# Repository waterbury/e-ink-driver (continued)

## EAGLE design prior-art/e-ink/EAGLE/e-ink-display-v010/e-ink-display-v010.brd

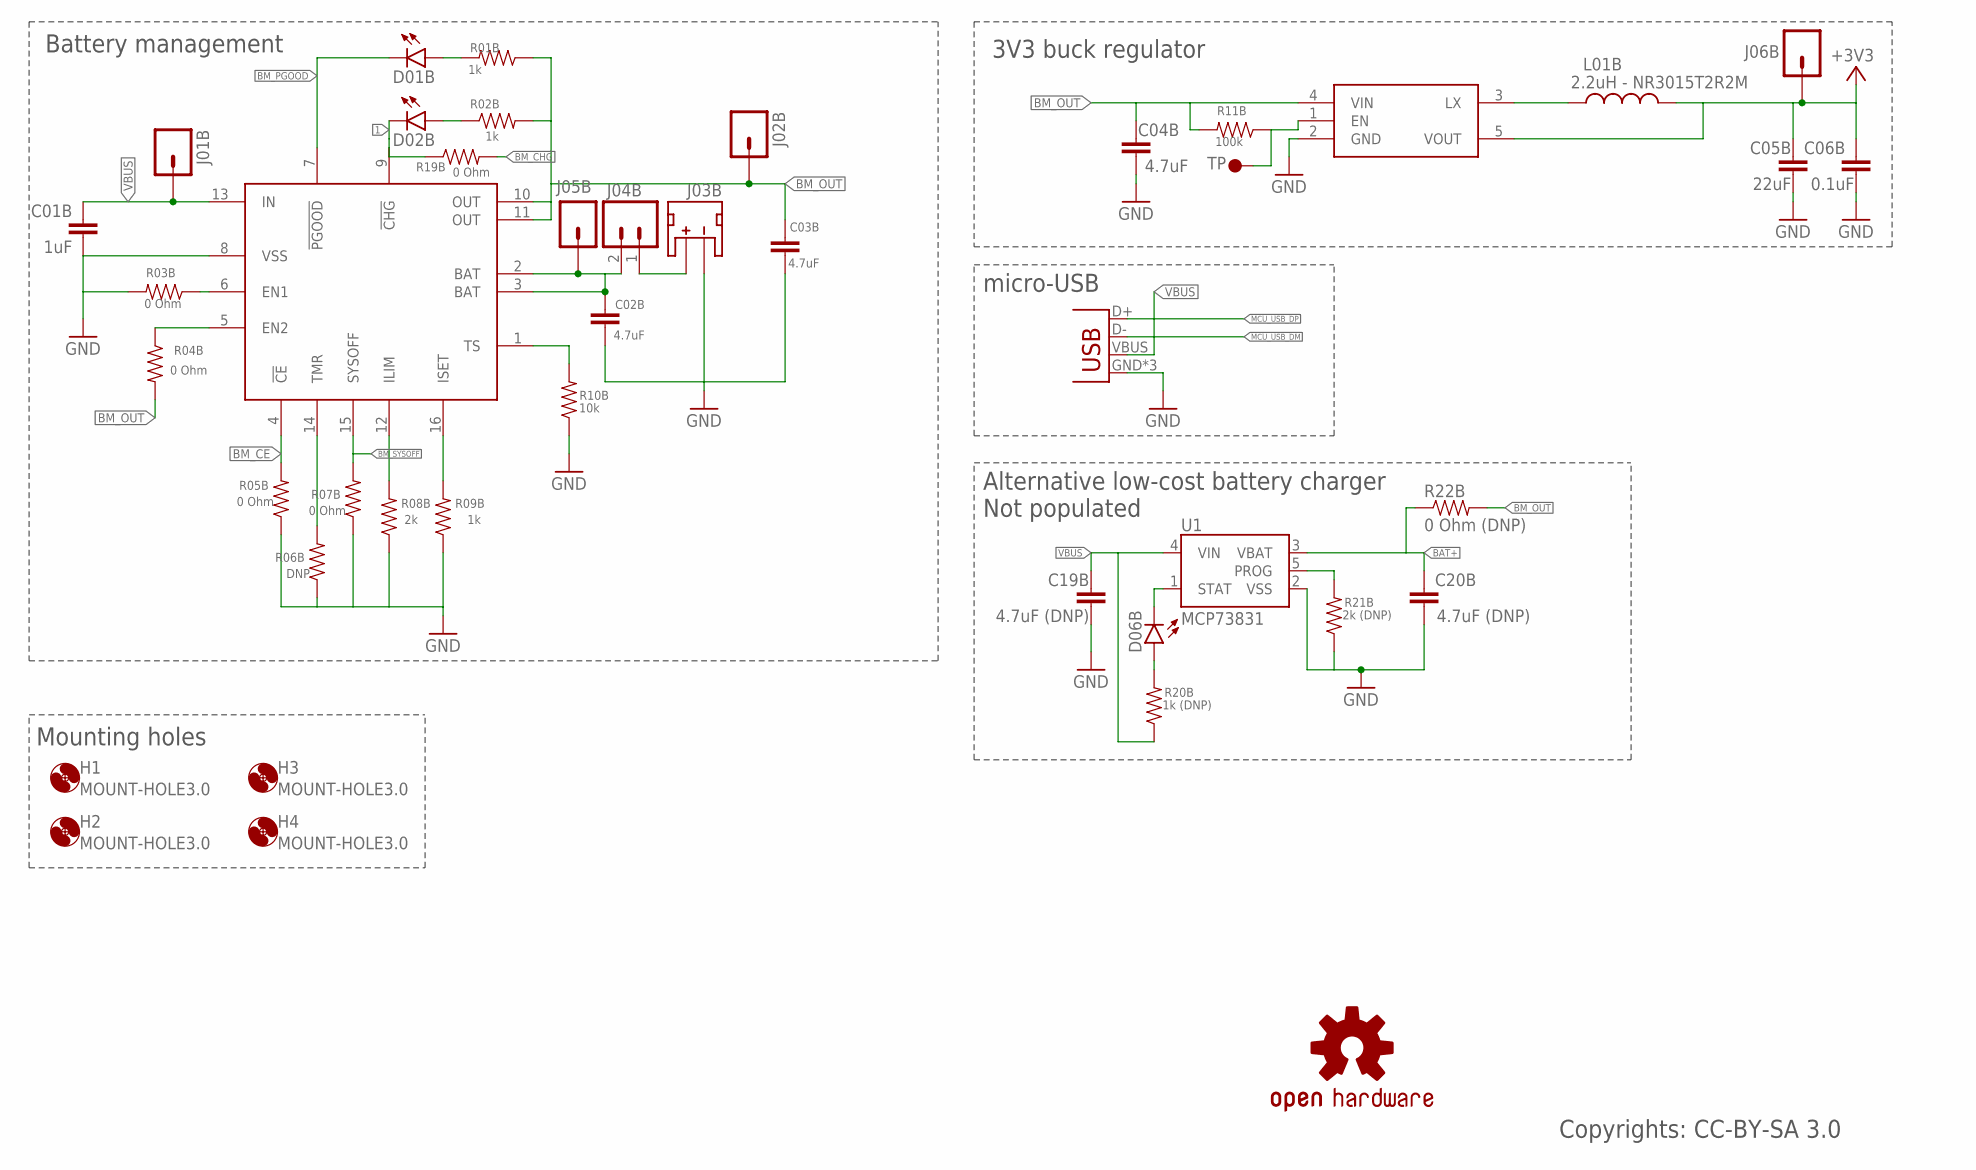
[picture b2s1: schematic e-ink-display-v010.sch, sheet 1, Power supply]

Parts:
C01B: 1uF; 0603-CAP
C02B, C03B, C04B: 4.7uF; 0603-CAP
C05B: 22uF; 0603-CAP
C06B: 0.1uF; 0603-CAP
C19B, C20B: 4.7uF (DNP); 0603-CAP
D01B, D02B, D06B: LED0603; LED-0603
H1, H2, H3, H4: MOUNT-HOLE3.0; 3,0
J01B, J02B, J05B, J06B: M01PTH; 1X01
J03B: JST_2MM_MALE; JST-2-SMD
J04B: M02PTH; 1X02
J07B: USBUSB-MICROB-SLOT-HOLE; USB-MICROB-SLOT-HOLE
L01B: 2.2uH - NR3015T2R2M; INDUCTOR-NR3015
LOGO1: OSHW-LOGOPAD; OSHW-LOGO-M-PAD
R01B, R02B, R09B: 1k; 0603-RES
R03B, R04B, R05B, R07B, R19B: 0 Ohm; 0603-RES
R06B: DNP; 0603-RES
R08B: 2k; 0603-RES
R10B: 10k; 0603-RES
R11B: 100k; 0603-RES
R20B: 1k (DNP); 0603-RES
R21B: 2k (DNP); 0603-RES
R22B: 0 Ohm (DNP); 1206
TP01B: TP1; TP35_BOT
U1: MCP73831; SOT23-5
U01B: BQ24075; PVQFN-16
U02B: R8008-33; SOT23-5

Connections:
1: D02B.C, R19B.1, U01B.9 (!CHG)
+3V3: C05B.2, C06B.2, J06B.1, L01B.2, U02B.5 (VOUT); also elsewhere on the board
BAT+: C20B.2, J03B.2 (+), J04B.1, R22B.1, U1.3 (VBAT)
BM_BAT: C02B.2, J04B.2, J05B.1, U01B.2 (BAT), U01B.3 (BAT)
BM_CE: R05B.2, U01B.4 (!CE)
BM_CHG: R19B.2; also elsewhere on the board
BM_OUT: C03B.2, C04B.2, J02B.1, R01B.1, R02B.2, R04B.2, R11B.2, R22B.2, U01B.10 (OUT), U01B.11 (OUT), U02B.4 (VIN); also elsewhere on the board
BM_PGOOD: D01B.C, U01B.7 (!PGOOD); also elsewhere on the board
BM_SYSOFF: R07B.2, U01B.15 (SYSOFF)
GND: C01B.1, C02B.1, C03B.1, C04B.1, C05B.1, C06B.1, C19B.1, C20B.1, J03B.1 (-), J07B.GND, J07B.MT1 (GND), J07B.MT2 (GND), R03B.2, R05B.1, R06B.1, R07B.1, R08B.1, R09B.1, R10B.1, R21B.1, U1.2 (VSS), U01B.8 (VSS), U02B.2 (GND); also elsewhere on the board
MCU_USB_DM: J07B.D-
MCU_USB_DP: J07B.D+
unnamed: R08B.2, U01B.12 (ILIM)
unnamed: R09B.2, U01B.16 (ISET)
unnamed: R04B.1, U01B.5 (EN2)
unnamed: R03B.1, U01B.6 (EN1)
unnamed: R06B.2, U01B.14 (TMR)
unnamed: R10B.2, U01B.1 (TS)
unnamed: D02B.A, R02B.1
unnamed: D01B.A, R01B.2
unnamed: R21B.2, U1.5 (PROG)
unnamed: R11B.1, TP01B.P$1, U02B.1 (EN)
unnamed: L01B.1, U02B.3 (LX)
unnamed: D06B.C, U1.1 (STAT)
unnamed: D06B.A, R20B.2
VBUS: C01B.2, C19B.2, J01B.1, J07B.VBUS, R20B.1, U1.4 (VIN), U01B.13 (IN)

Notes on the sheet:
Battery management
3V3 buck regulator
micro-USB
Mounting holes
Alternative low-cost battery charger Not populated
Copyrights: CC-BY-SA 3.0

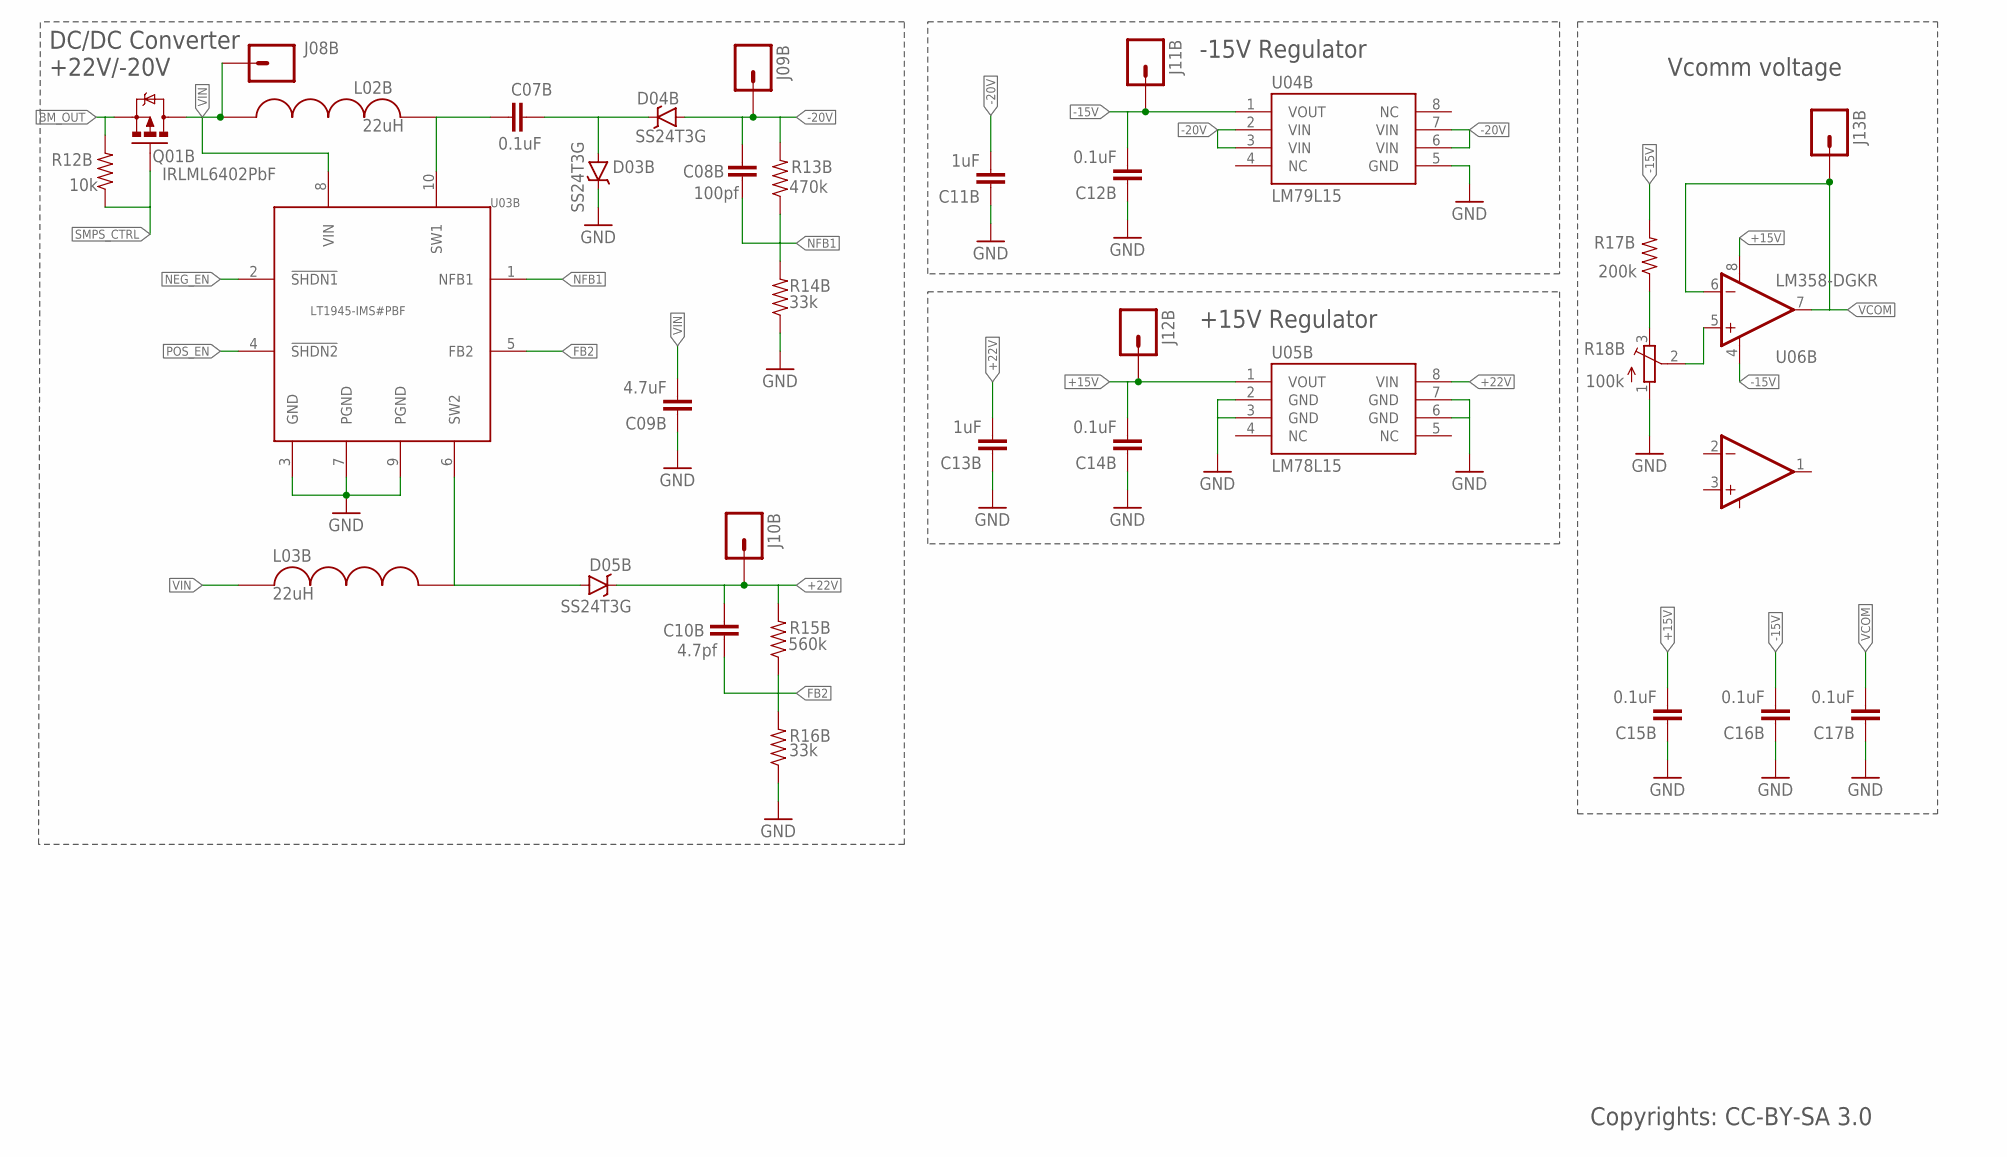
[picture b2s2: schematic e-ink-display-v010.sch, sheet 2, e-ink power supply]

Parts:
C07B, C12B, C14B, C15B, C16B, C17B: 0.1uF; 0603-CAP
C08B: 100pf; 0603-CAP
C09B: 4.7uF; 0603-CAP
C10B: 4.7pf; 0603-CAP
C11B, C13B: 1uF; 0603-CAP
D03B, D04B, D05B: SS24T3G; SMA-DIODE
J08B, J09B, J10B, J11B, J12B, J13B: M01PTH; 1X01
L02B, L03B: 22uH; 4040(1515)
Q01B: IRLML6402PbF; SOT23-3
R12B: 10k; 0603-RES
R13B: 470k; 0603-RES
R14B, R16B: 33k; 0603-RES
R15B: 560k; 0603-RES
R17B: 200k; 0603-RES
R18B: 100k; TC33X
U03B: LT1945-IMS#PBF; MSOP-10
U04B: LM79L15; SO08
U05B: LM78L15; SO08
U06B: LM358-DGKR; MSOP-8

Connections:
+15V: C14B.2, C15B.2, J12B.1, U05B.1 (VOUT), U06B.8 (V+); also elsewhere on the board
+22V: C10B.2, C13B.2, D05B.C, J10B.1, R15B.2, U05B.8 (VIN); also elsewhere on the board
-15V: C12B.2, C16B.2, J11B.1, R17B.2, U04B.1 (VOUT), U06B.4 (V-); also elsewhere on the board
-20V: C08B.2, C11B.2, D04B.A, J09B.1, R13B.2, U04B.2 (VIN), U04B.3 (VIN), U04B.6 (VIN), U04B.7 (VIN); also elsewhere on the board
BM_OUT: Q01B.2 (S), R12B.2; also elsewhere on the board
FB2: C10B.1, R15B.1, R16B.2, U03B.5 (FB2)
GND: C09B.1, C11B.1, C12B.1, C13B.1, C14B.1, C15B.1, C16B.1, C17B.1, D03B.C, R14B.1, R16B.1, R18B.1 (A), U03B.3 (GND), U03B.7 (PGND), U03B.9 (PGND), U04B.5 (GND), U05B.2 (GND), U05B.3 (GND), U05B.6 (GND), U05B.7 (GND); also elsewhere on the board
unnamed: C07B.1, L02B.P$2, U03B.10 (SW1)
unnamed: C07B.2, D03B.A, D04B.C
unnamed: R18B.2 (S), U06B.5 (+IN2)
unnamed: R17B.1, R18B.3 (E)
unnamed: D05B.A, L03B.P$2, U03B.6 (SW2)
NEG_EN: U03B.2 (!SHDN1); also elsewhere on the board
NFB1: C08B.1, R13B.1, R14B.2, U03B.1 (NFB1)
POS_EN: U03B.4 (!SHDN2); also elsewhere on the board
SMPS_CTRL: Q01B.1 (G), R12B.1; also elsewhere on the board
VCOM: C17B.2, J13B.1, U06B.6 (-IN2), U06B.7 (OUT2); also elsewhere on the board
VIN: C09B.2, J08B.1, L02B.P$1, L03B.P$1, Q01B.3 (D), U03B.8 (VIN)

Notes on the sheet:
-15V Regulator
+15V Regulator
Vcomm voltage
DC/DC Converter +22V/-20V
Copyrights: CC-BY-SA 3.0

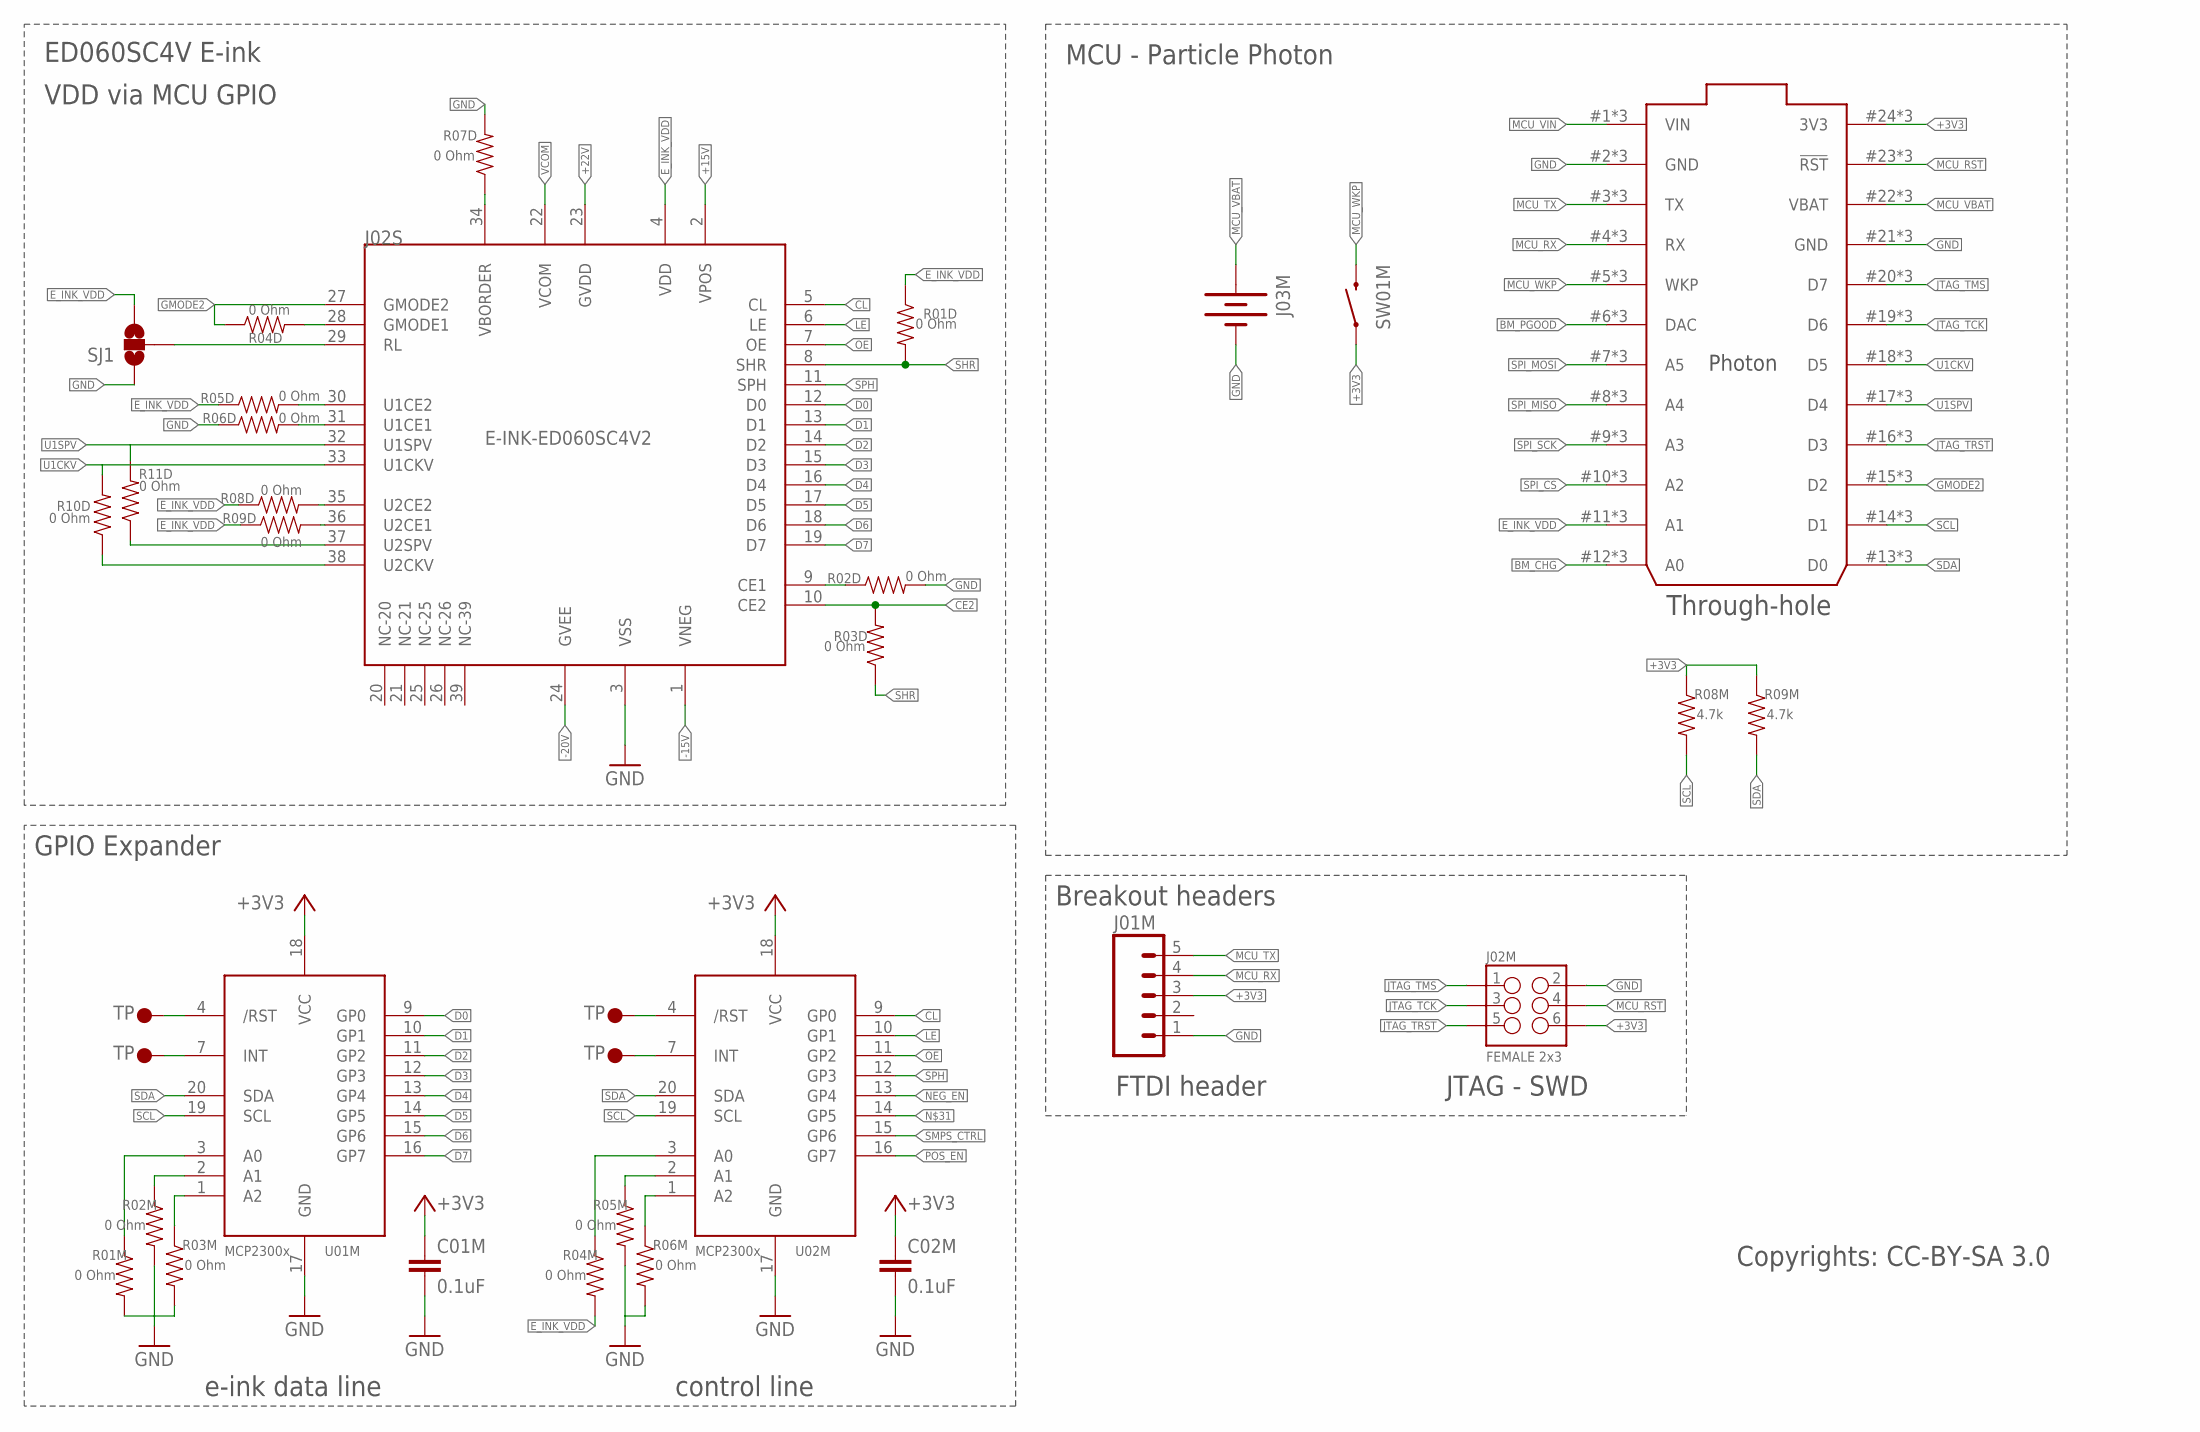
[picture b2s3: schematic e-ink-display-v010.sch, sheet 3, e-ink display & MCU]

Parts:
C01M, C02M: 0.1uF; 0603-CAP
J01M: M05PTH; 1X05
J02M: FEMALE 2x3; 2X3
J02S: E-INK-ED060SC4V2; FPC-0.3-39
J03M: BATTERY20PTH; BATTCOM_20MM_PTH
R01D, R01M, R02D, R02M, R03D, R03M, R04D, R04M, R05D, R05M, R06D, R06M, R07D, R08D, R09D, R10D, R11D: 0 Ohm; 0603-RES
R08M, R09M: 4.7k; 0603-RES
SJ1: SOLDERJUMPER_2WAYT; SJ_2
SW01M: SWITCH-MOMENTARY-2PTH; TACTILE-PTH
U01M, U02M: MCP2300X/QFN; QFN-20(4X4)
U03M: PHOTON_WITH_STACKABLE_HEADERS; PHOTON_STACKABLE
U$1, U$2, U$3, U$4: TP1; TP35_BOT

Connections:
+3V3: C01M.1, C02M.1, J01M.3, J02M.6, R08M.1, R09M.1, SW01M.1, U01M.18 (VCC), U02M.18 (VCC), U03M.24 (3V3), U03M.#24 (3V3), U03M.@24 (3V3); also elsewhere on the board
+15V: J02S.2 (VPOS); also elsewhere on the board
+22V: J02S.23 (GVDD); also elsewhere on the board
-15V: J02S.1 (VNEG); also elsewhere on the board
-20V: J02S.24 (GVEE); also elsewhere on the board
BM_CHG: U03M.12 (A0), U03M.#12 (A0), U03M.@12 (A0); also elsewhere on the board
BM_PGOOD: U03M.6 (DAC), U03M.#6 (DAC), U03M.@6 (DAC); also elsewhere on the board
CE2: J02S.10 (CE2), R03D.2
CL: J02S.5 (CL), U02M.9 (GP0)
D0: J02S.12 (D0), U01M.9 (GP0)
D1: J02S.13 (D1), U01M.10 (GP1)
D2: J02S.14 (D2), U01M.11 (GP2)
D3: J02S.15 (D3), U01M.12 (GP3)
D4: J02S.16 (D4), U01M.13 (GP4)
D5: J02S.17 (D5), U01M.14 (GP5)
D6: J02S.18 (D6), U01M.15 (GP6)
D7: J02S.19 (D7), U01M.16 (GP7)
E_INK_VDD: J02S.4 (VDD), R01D.1, R04M.2, R05D.1, R08D.1, R09D.1, SJ1.3, U03M.11 (A1), U03M.#11 (A1), U03M.@11 (A1)
GMODE2: J02S.27 (GMODE2), R04D.1, U03M.15 (D2), U03M.#15 (D2), U03M.@15 (D2)
GND: C01M.2, C02M.2, J01M.1, J02M.2, J02S.3 (VSS), J03M.2 (-), R01M.2, R02D.2, R02M.2, R03M.2, R05M.2, R06D.1, R06M.2, R07D.2, SJ1.1, U01M.17 (GND), U02M.17 (GND), U03M.2 (GND), U03M.21 (GND), U03M.#2 (GND), U03M.#21 (GND), U03M.@2 (GND), U03M.@21 (GND); also elsewhere on the board
JTAG_TCK: J02M.3, U03M.19 (D6), U03M.#19 (D6), U03M.@19 (D6)
JTAG_TMS: J02M.1, U03M.20 (D7), U03M.#20 (D7), U03M.@20 (D7)
JTAG_TRST: J02M.5, U03M.16 (D3), U03M.#16 (D3), U03M.@16 (D3); also elsewhere on the board
LE: J02S.6 (LE), U02M.10 (GP1)
MCU_RST: J02M.4, U03M.23 (!RST), U03M.#23 (!RST), U03M.@23 (!RST)
MCU_RX: J01M.4, U03M.4 (RX), U03M.#4 (RX), U03M.@4 (RX)
MCU_TX: J01M.5, U03M.3 (TX), U03M.#3 (TX), U03M.@3 (TX)
MCU_VBAT: J03M.1 (+), U03M.22 (VBAT), U03M.#22 (VBAT), U03M.@22 (VBAT)
MCU_VIN: U03M.1 (VIN), U03M.#1 (VIN), U03M.@1 (VIN)
MCU_WKP: SW01M.3 (2), U03M.5 (WKP), U03M.#5 (WKP), U03M.@5 (WKP)
unnamed: J02S.28 (GMODE1), R04D.2
unnamed: J02S.31 (U1CE1), R06D.2
unnamed: U01M.4 (/RST), U$1.P$1
unnamed: U01M.7 (INT), U$2.P$1
unnamed: U02M.4 (/RST), U$3.P$1
unnamed: U02M.7 (INT), U$4.P$1
unnamed: R03M.1, U01M.1 (A2)
unnamed: R01M.1, U01M.3 (A0)
unnamed: J02S.35 (U2CE2), R08D.2
unnamed: J02S.36 (U2CE1), R09D.2
unnamed: J02S.9 (CE1), R02D.1
unnamed: J02S.34 (VBORDER), R07D.1
unnamed: R06M.1, U02M.1 (A2)
unnamed: R05M.1, U02M.2 (A1)
unnamed: R04M.1, U02M.3 (A0)
unnamed: R02M.1, U01M.2 (A1)
NEG_EN: U02M.13 (GP4); also elsewhere on the board
OE: J02S.7 (OE), U02M.11 (GP2)
POS_EN: U02M.16 (GP7); also elsewhere on the board
RL: J02S.29 (RL), SJ1.2
SCL: R08M.2, U01M.19 (SCL), U02M.19 (SCL), U03M.14 (D1), U03M.#14 (D1), U03M.@14 (D1); also elsewhere on the board
SDA: R09M.2, U01M.20 (SDA), U02M.20 (SDA), U03M.13 (D0), U03M.#13 (D0), U03M.@13 (D0); also elsewhere on the board
SHR: J02S.8 (SHR), R01D.2, R03D.1
SMPS_CTRL: U02M.15 (GP6); also elsewhere on the board
SPH: J02S.11 (SPH), U02M.12 (GP3)
SPI_CS: U03M.10 (A2), U03M.#10 (A2), U03M.@10 (A2); also elsewhere on the board
SPI_MISO: U03M.8 (A4), U03M.#8 (A4), U03M.@8 (A4); also elsewhere on the board
SPI_MOSI: U03M.7 (A5), U03M.#7 (A5), U03M.@7 (A5); also elsewhere on the board
SPI_SCK: U03M.9 (A3), U03M.#9 (A3), U03M.@9 (A3); also elsewhere on the board
U1CE2: J02S.30 (U1CE2), R05D.2
U1CKV: J02S.33 (U1CKV), R10D.2, U03M.18 (D5), U03M.#18 (D5), U03M.@18 (D5)
U1SPV: J02S.32 (U1SPV), R11D.2, U03M.17 (D4), U03M.#17 (D4), U03M.@17 (D4)
U2CKV: J02S.38 (U2CKV), R10D.1
U2SPV: J02S.37 (U2SPV), R11D.1
VCOM: J02S.22 (VCOM); also elsewhere on the board

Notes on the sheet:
ED060SC4V E-ink VDD via MCU GPIO
Through-hole
MCU - Particle Photon
Breakout headers
GPIO Expander
e-ink data line
control line
FTDI header
JTAG - SWD
Copyrights: CC-BY-SA 3.0

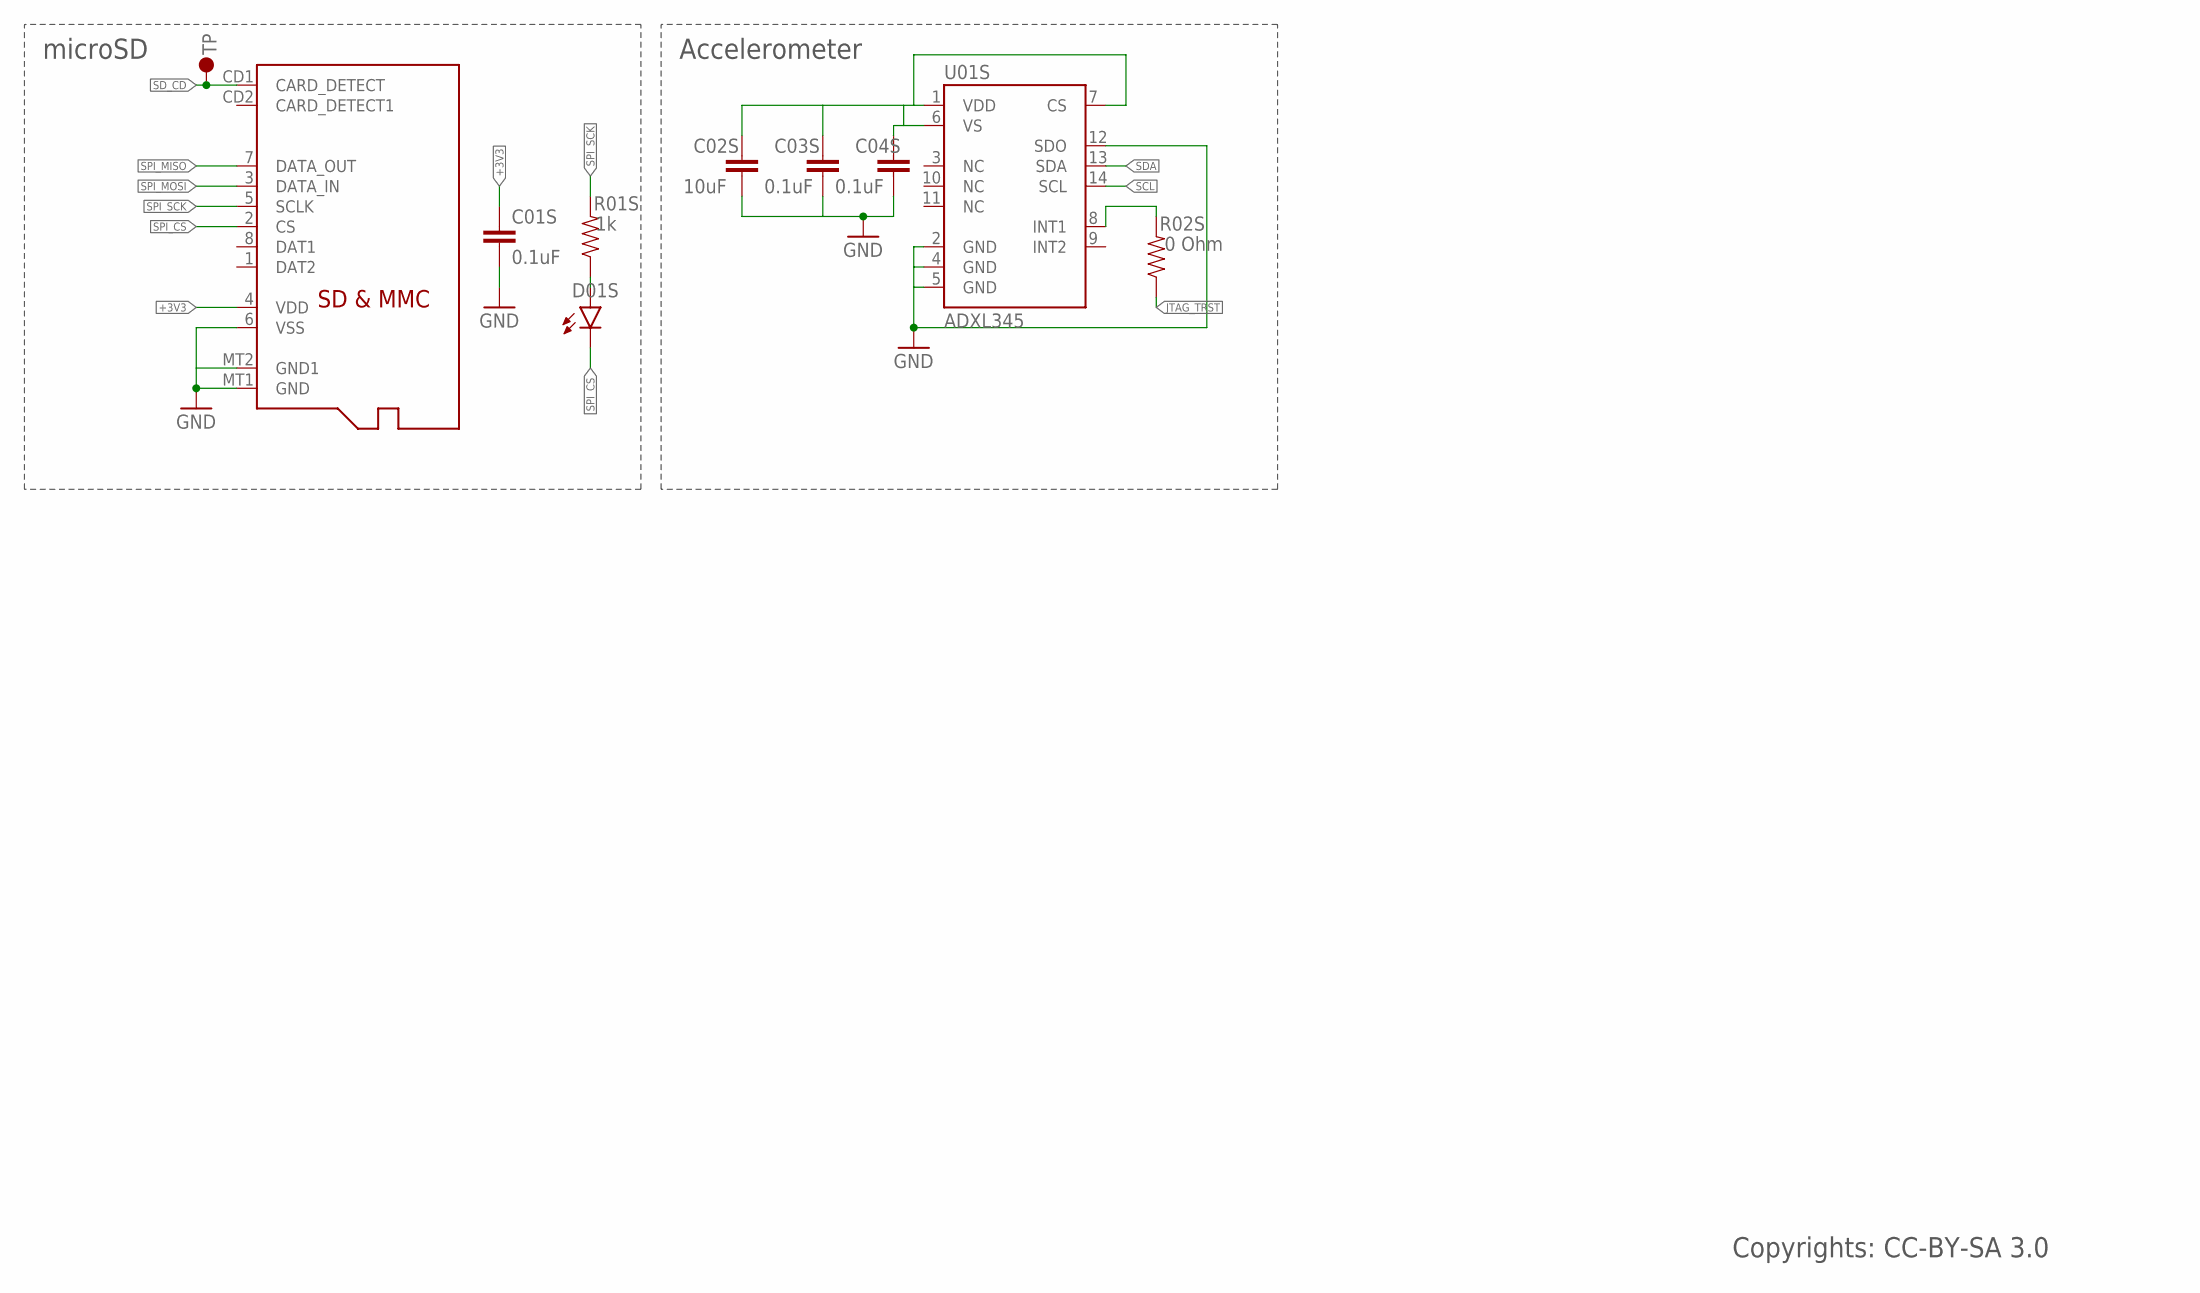
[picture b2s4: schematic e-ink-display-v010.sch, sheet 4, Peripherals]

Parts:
C01S, C03S, C04S: 0.1uF; 0603-CAP
C02S: 10uF; 0603-CAP
D01S: LED0603; LED-0603
J01S: MICROSD
R01S: 1k; 0603-RES
R02S: 0 Ohm; 0603-RES
U01S: ADXL345; LGA14
U$5: TP3; TP60_BOT

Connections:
+3V3: C01S.1, J01S.4 (VDD); also elsewhere on the board
GND: C01S.2, C02S.2, C03S.2, C04S.2, J01S.6 (VSS), J01S.MT1 (GND), J01S.MT2 (GND1), U01S.2 (GND), U01S.4 (GND), U01S.5 (GND), U01S.12 (SDO); also elsewhere on the board
JTAG_TRST: R02S.1; also elsewhere on the board
unnamed: R02S.2, U01S.8 (INT1)
unnamed: C02S.1, C03S.1, C04S.1, U01S.1 (VDD), U01S.6 (VS), U01S.7 (CS)
R01S: D01S.A, R01S.1
SCL: U01S.14 (SCL); also elsewhere on the board
SDA: U01S.13 (SDA); also elsewhere on the board
SD_CD: J01S.CD1 (CARD_DETECT), U$5.P$1
SPI_CS: D01S.C, J01S.2 (CS); also elsewhere on the board
SPI_MISO: J01S.7 (DATA_OUT); also elsewhere on the board
SPI_MOSI: J01S.3 (DATA_IN); also elsewhere on the board
SPI_SCK: J01S.5 (SCLK), R01S.2; also elsewhere on the board

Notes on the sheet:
microSD
Accelerometer
Copyrights: CC-BY-SA 3.0

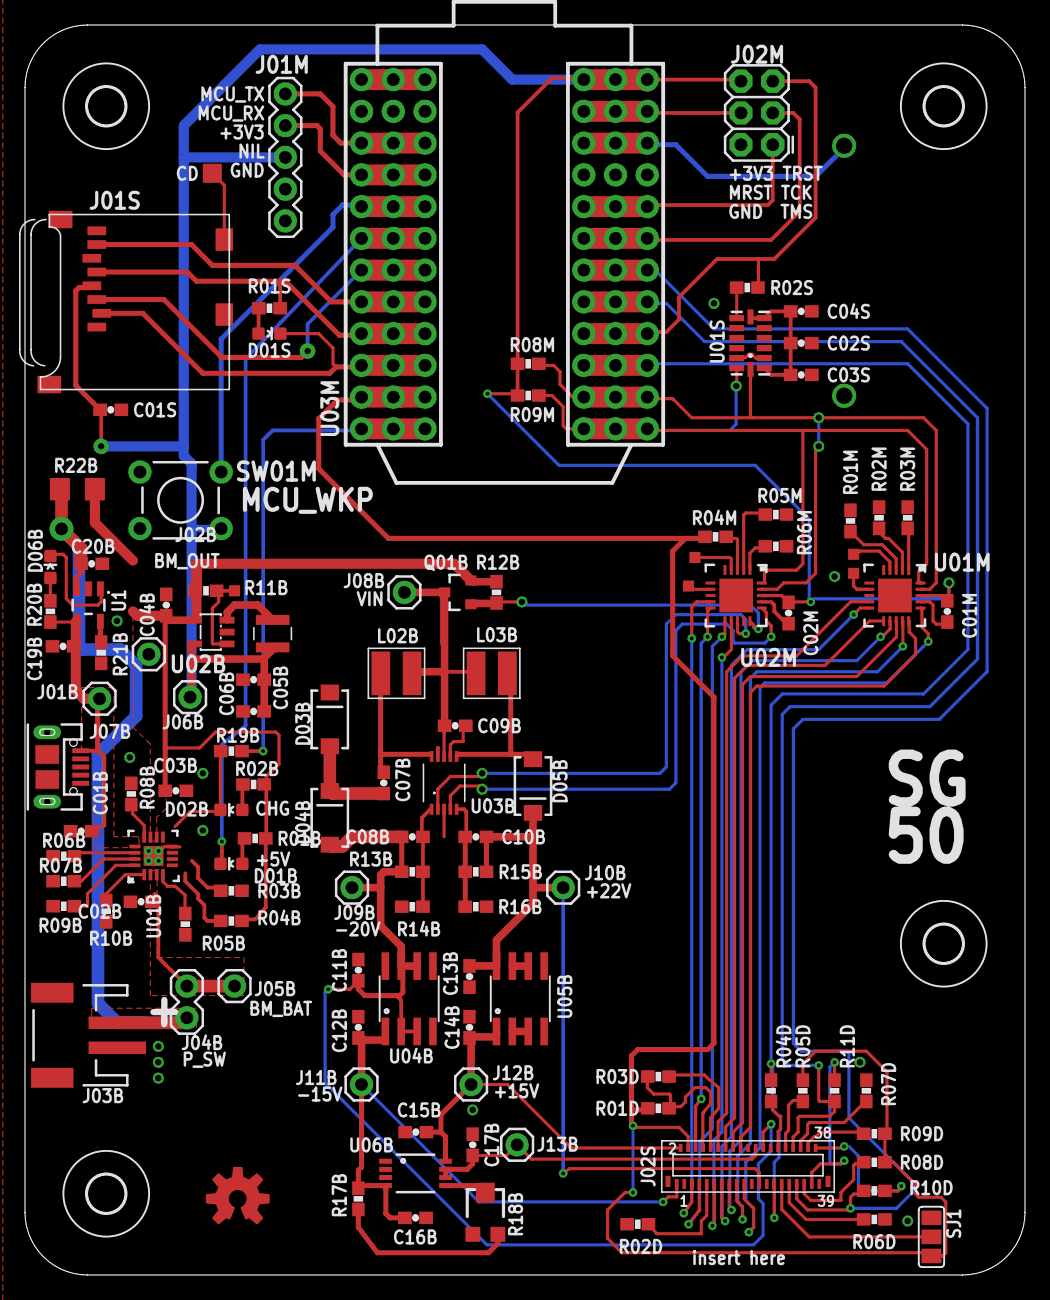
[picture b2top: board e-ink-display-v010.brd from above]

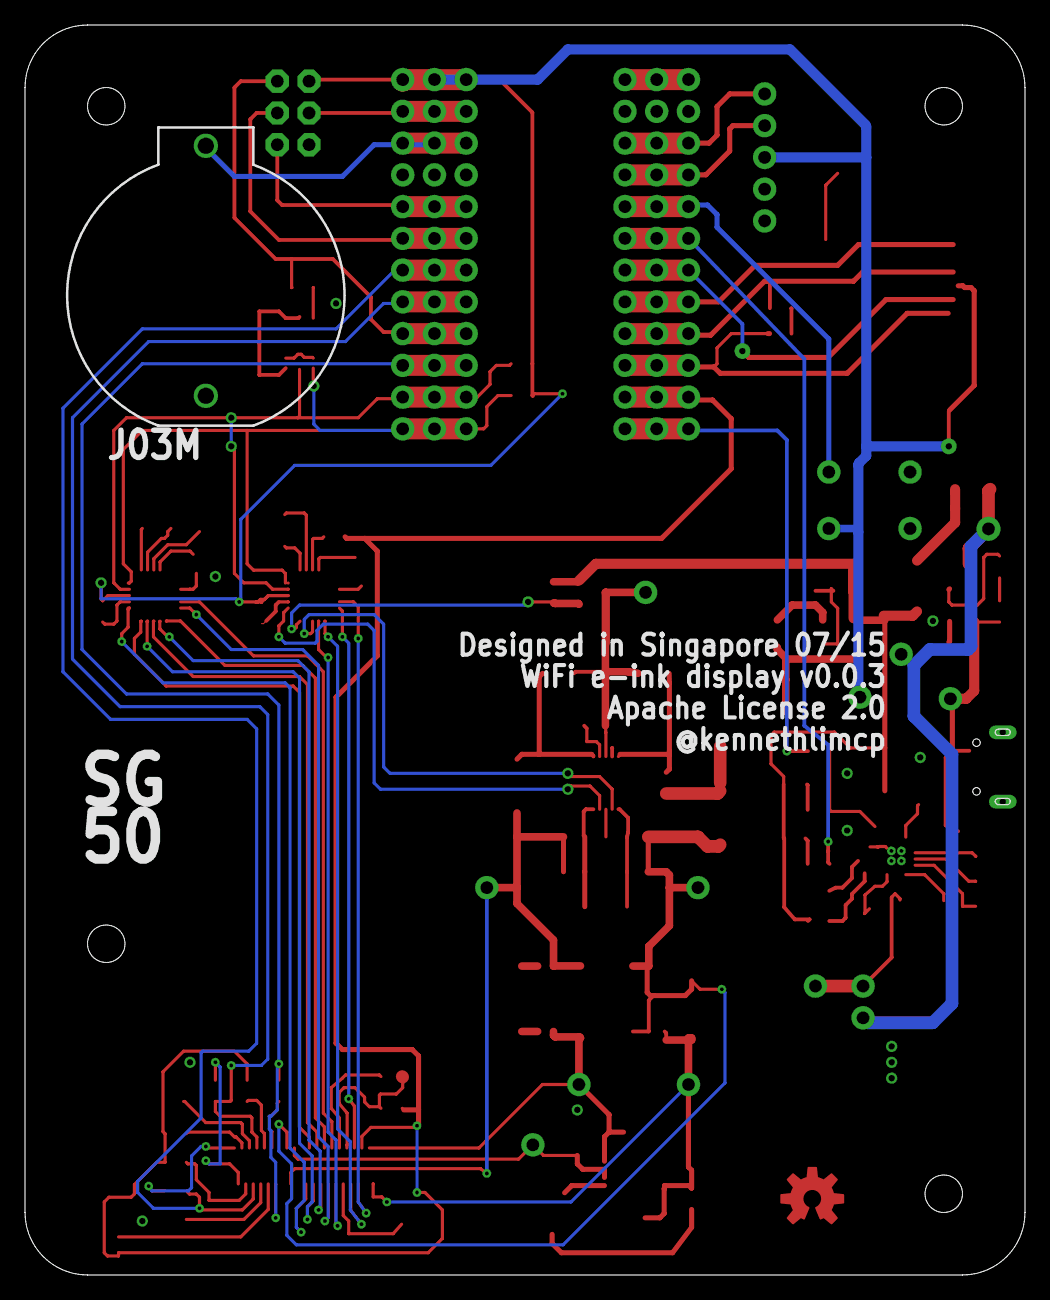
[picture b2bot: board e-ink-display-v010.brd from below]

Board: 4 copper layers, 80.0 x 100.0 mm, 121 parts (7 on the bottom side), 97 nets.

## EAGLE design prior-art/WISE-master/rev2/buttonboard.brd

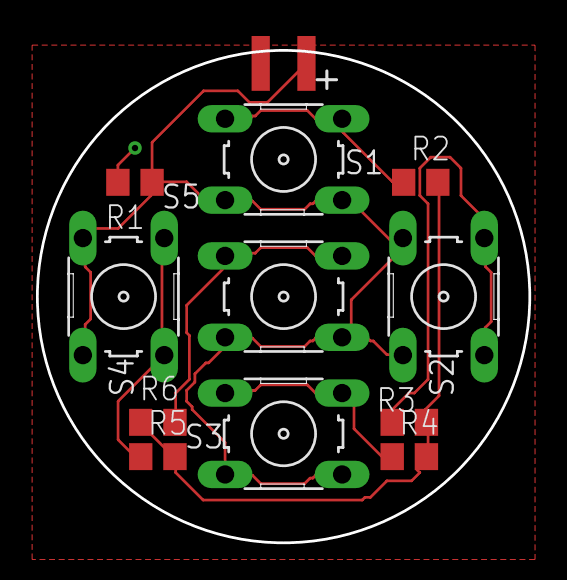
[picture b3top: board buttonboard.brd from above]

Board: 2 copper layers, 27.4 x 27.4 mm, 12 parts (0 on the bottom side), 7 nets.

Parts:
R1, R4: 10k; R0805
R2: 1K; R0805
R3: 2k; R0805
R5: 12k; R0805
R6: 39k; R0805
S1, S2, S3, S4, S5: B3F-10XX
U$1: EDGE_CON; EDGE_CON_2

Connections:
+3V3: R2.2, R3.2, R4.2, R5.2, R6.2
DPAD: R1.1, S1.3, S1.4, S2.3, S2.4, S3.3, S3.4, S4.3, S4.4, S5.3, S5.4, U$1.1
unnamed: R2.1, S1.1, S1.2
unnamed: R3.1, S2.1, S2.2
unnamed: R4.1, S3.1, S3.2
unnamed: R5.1, S4.1, S4.2
unnamed: R6.1, S5.1, S5.2

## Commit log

2017-04-05 fix: markdown format
2017-04-05 add: rf resources
2017-04-22 add: hardware product development process
2017-04-23 add: Converting Seeed OPL EagleCAD library to KiCad
2017-05-17 add: Wireless Protocols for IoT Devices
2017-06-01 add: Article on capacitor temp and V rating
2017-06-16 Add: Minimizing Converter High-Frequency Switching Noise
2017-07-07 fix: markdown formatting
2017-07-17 add: EMC appnote
2017-07-17 add: Tetronix oscilloscope guide
2017-08-14 add: pdf for eink schematic
2017-08-14 fix: README markdown and wording
2017-09-11 add: initial notes about certification
2017-09-11 add: CAN bus resource
2017-11-19 add: certification for manufacturnig
2017-11-19 add: certification for quality
2017-11-19 add: tests information
2017-11-19 add: burn-in test
2017-11-19 add: thermal cycling test
2018-01-13 add: MIL-PRF-38535
2018-01-13 fix: markdown
2018-12-31 added in Teds stuff from dropbox
2019-01-01 Added ESP / WISE e-ink driver
2019-01-02 removed extraneous files, reorganized dirs, removed license, updated readme
2019-01-06 added power sequencing doc
2019-01-06 added note about ESP32 modules
2019-01-06 added power rail table
2019-01-06 Fixed some formatting issues with table and sequence list
2019-01-14 adding the kicad stuff. just the +20V/-22V supply for now
2019-01-14 added my kicad library
2019-01-20 added VCOM conditioner
2019-01-20 added 3.3v buck and annotations. PSUs done
2019-02-04 reorganized schems and added a note about buffer
2019-02-25 added 74LCX16244
2019-02-25 removed confusing duplicate lib folder
2019-11-19 I think the schematic is done. ugly but feature-complete
2019-11-20 added additional SMPS control transistor circuit
2019-11-20 added not about passive size
2019-12-03 recovered from an unplanned poweroff, and removed backup files
2019-12-03 added lines to not sync backup files and autosaves
2021-11-10 Update README.md
    https://forum.kicad.info/t/warning-avoid-all-links-to-kicad-pcb-org-use-kicad-org/31521
2023-03-19 test
